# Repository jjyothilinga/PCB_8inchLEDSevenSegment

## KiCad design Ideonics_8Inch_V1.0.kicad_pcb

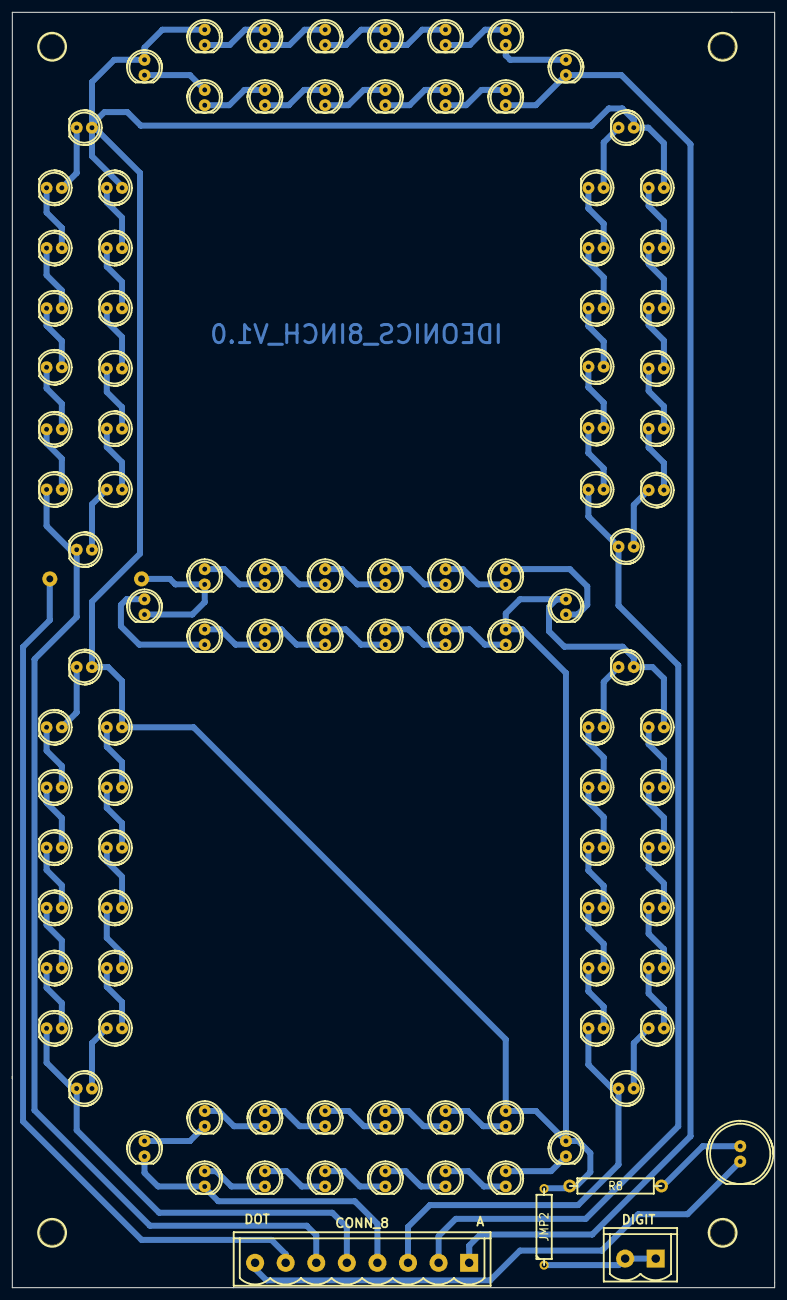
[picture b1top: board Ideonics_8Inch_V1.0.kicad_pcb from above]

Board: 2 copper layers, 126.6 x 211.8 mm, 108 parts (1 on the bottom side), 96 nets.

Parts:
1PIN, 1PIN#2, 1PIN#3, 1PIN#4: P***; 1pin
D1, D5, D6, D13, D14, D21, D22, D29, D30, D40, D78, D79, D86, D87: LED_A; led_5mm_red
D2, D7, D8, D15, D16, D23, D24, D31, D32, D39, D76, D77, D88, D89: LED_B; led_5mm_red
D3, D9, D10, D17, D18, D25, D26, D33, D34, D37, D72, D73, D90, D91: LED_C; led_5mm_red
D4, D11, D12, D19, D20, D27, D28, D35, D36, D38, D74, D75, D92, D93: LED_D; led_5mm_red
D41, D44, D45, D50, D51, D56, D57, D62, D63, D68, D80, D81, D96, D97: LED_E; led_5mm_red
D42, D46, D47, D52, D53, D58, D59, D64, D65, D69, D82, D83, D98, D99: LED_F; led_5mm_red
D43, D48, D49, D54, D55, D60, D61, D66, D67, D70, D84, D85, D94, D95: LED_G; led_5mm_red
D71: LED_DOT; led_10mm_red
JMP1: JMP; R6
JMP2: JMP; R5
P1: CONN_8; mstbva_2,5/8-g-5,08
P3: CONN_2; mstbva_2,5/2-g-5,08
R8: R; R6

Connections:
/A: D1.1, D2.1, D3.1, D4.1, D6.1, D8.1, D10.1, D12.1, D41.1, D42.1, D43.1, D45.1, D47.1, D49.1, JMP2.2, R8.1
/CA1: JMP2.1, P3.1, P3.2
/DOT: D71.2, P1.8
/G: D70.2, D94.2, JMP1.2
/SEG A: D40.2, D86.2, P1.1
/SEG B: D39.2, D88.2, P1.2
/SEG C: D37.2, D90.2, P1.3
/SEG D: D38.2, D92.2, P1.4
/SEG E: D68.2, D96.2, P1.5
/SEG F: D69.2, D98.2, P1.6
/SEG G: JMP1.1, P1.7
unnamed: D17.2, D25.1
unnamed: D35.2, D74.1
unnamed: D36.2, D75.1
unnamed: D28.2, D36.1
unnamed: D20.2, D28.1
unnamed: D12.2, D20.1
unnamed: D26.2, D34.1
unnamed: D34.2, D73.1
unnamed: D33.2, D72.1
unnamed: D25.2, D33.1
unnamed: D27.2, D35.1
unnamed: D18.2, D26.1
unnamed: D10.2, D18.1
unnamed: D9.2, D17.1
unnamed: D3.2, D9.1
unnamed: D8.2, D16.1
unnamed: D51.2, D57.1
unnamed: D47.2, D53.1
unnamed: D53.2, D59.1
unnamed: D52.2, D58.1
unnamed: D58.2, D64.1
unnamed: D59.2, D65.1
unnamed: D65.2, D83.1
unnamed: D64.2, D82.1
unnamed: D62.2, D80.1
unnamed: D57.2, D63.1
unnamed: D56.2, D62.1
unnamed: D50.2, D56.1
unnamed: D16.2, D24.1
unnamed: D45.2, D51.1
unnamed: D44.2, D50.1
unnamed: D41.2, D44.1
unnamed: D11.2, D19.1
unnamed: D4.2, D11.1
unnamed: D19.2, D27.1
unnamed: D75.2, D93.1
unnamed: D74.2, D92.1
unnamed: D73.2, D91.1
unnamed: D72.2, D90.1
unnamed: D39.1, D89.2
unnamed: D77.2, D89.1
unnamed: D76.2, D88.1
unnamed: D79.2, D87.1
unnamed: D78.2, D86.1
unnamed: D85.2, D95.1
unnamed: D84.2, D94.1
unnamed: D81.2, D97.1
unnamed: D80.2, D96.1
unnamed: D22.2, D30.1
unnamed: D24.2, D32.1
unnamed: D32.2, D77.1
unnamed: D31.2, D76.1
unnamed: D23.2, D31.1
unnamed: D15.2, D23.1
unnamed: D7.2, D15.1
unnamed: D2.2, D7.1
unnamed: D29.2, D78.1
unnamed: D30.2, D79.1
unnamed: D21.2, D29.1
unnamed: D14.2, D22.1
unnamed: D13.2, D21.1
unnamed: D5.2, D13.1
unnamed: D6.2, D14.1
unnamed: D1.2, D5.1
unnamed: D83.2, D99.1
unnamed: D82.2, D98.1
unnamed: D38.1, D93.2
unnamed: D37.1, D91.2
unnamed: D40.1, D87.2
unnamed: D70.1, D95.2
unnamed: D69.1, D99.2
unnamed: D54.2, D60.1
unnamed: D48.2, D54.1
unnamed: D43.2, D48.1
unnamed: D49.2, D55.1
unnamed: D55.2, D61.1
unnamed: D61.2, D67.1
unnamed: D60.2, D66.1
unnamed: D66.2, D84.1
unnamed: D46.2, D52.1
unnamed: D42.2, D46.1
unnamed: D68.1, D97.2
unnamed: D63.2, D81.1
unnamed: D67.2, D85.1
unnamed: D71.1, R8.2

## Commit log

2016-02-05 :space_invader: Added .gitattributes & .gitignore files
2016-02-05 Completed
